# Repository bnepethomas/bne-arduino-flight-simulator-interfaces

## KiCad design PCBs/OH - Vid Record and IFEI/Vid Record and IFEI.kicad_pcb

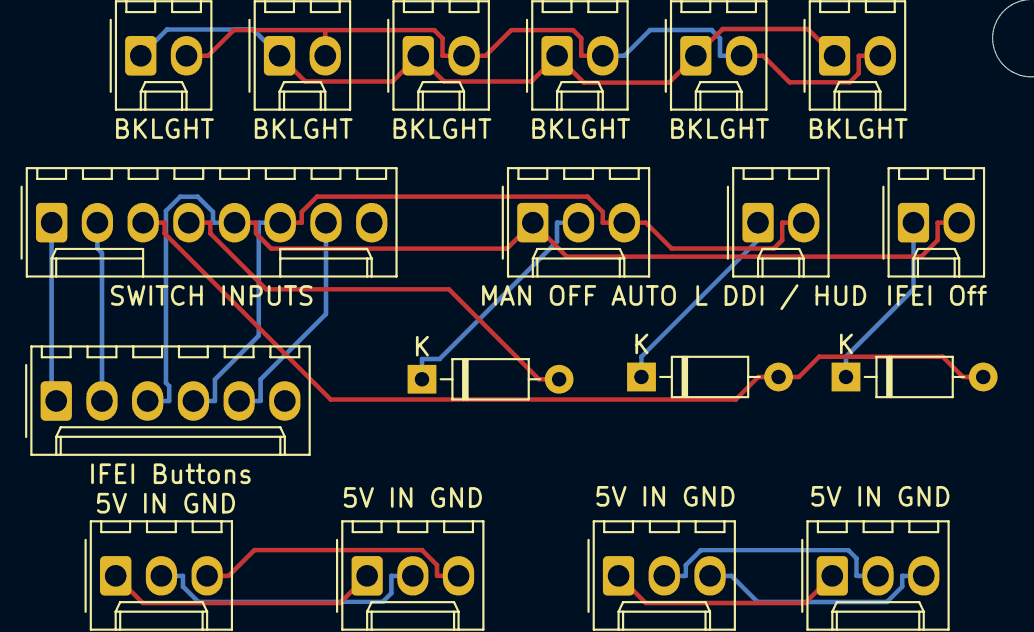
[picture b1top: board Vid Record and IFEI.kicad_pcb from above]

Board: 2 copper layers, 22 parts (0 on the bottom side), 18 nets.

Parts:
D1, D2, D3: D; D_Signal_P7.62mm_Horizontal
H1, H2, H3, H4: MountingHole; MountingHole_4.3mm_M4
J1: IFEI NEXTION; Molex_1x03_P2.54mm_Vertical
J2: IFEI BRIGHTNESS; Molex_1x03_P2.54mm_Vertical
J3: IFEI Buttons; Molex_1x06_P2.54mm_Vertical
J4: SWITCH INPUTS; Molex_1x08_P2.54mm_Vertical
J5, J6, J7, J8, J9, J10: BKLGHT; Molex_1x02_P2.54mm_Vertical
RV1: IFEI NEXTRON; Molex_1x03_P2.54mm_Vertical
RV2: IFEI Brightness; Molex_1x03_P2.54mm_Vertical
SW1: IFEI Off; Molex_1x02_P2.54mm_Vertical
SW2: L DDI / HUD; Molex_1x02_P2.54mm_Vertical
SW3: MAN OFF AUTO; Molex_1x03_P2.54mm_Vertical

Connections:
/BACKLIGHT+12V: J5.1, J6.1, J7.1, J8.1, J9.1, J10.1
/BACKLIGHT-GND: J5.2, J6.2, J7.2, J8.2, J9.2, J10.2
/COL-3: D1.2, D2.2, J4.3
/COL-4: D3.2, J4.4
/IFEI-COL-1: J3.1, J4.1
/IFEI-COL-2: J3.2, J4.2
/IFEI-ROW-1: J3.3, J4.5, SW1.2, SW3.1
/IFEI-ROW-2: J3.4, J4.6, SW2.2, SW3.3
/IFEI-ROW-3: J3.5, J4.7
unnamed: D1.1, SW1.1
unnamed: D2.1, SW2.1
unnamed: D3.1, SW3.2
unnamed: J1.1, RV1.1
unnamed: J1.2, RV1.2
unnamed: J1.3, RV1.3
unnamed: J2.1, RV2.1
unnamed: J2.2, RV2.2
unnamed: J2.3, RV2.3

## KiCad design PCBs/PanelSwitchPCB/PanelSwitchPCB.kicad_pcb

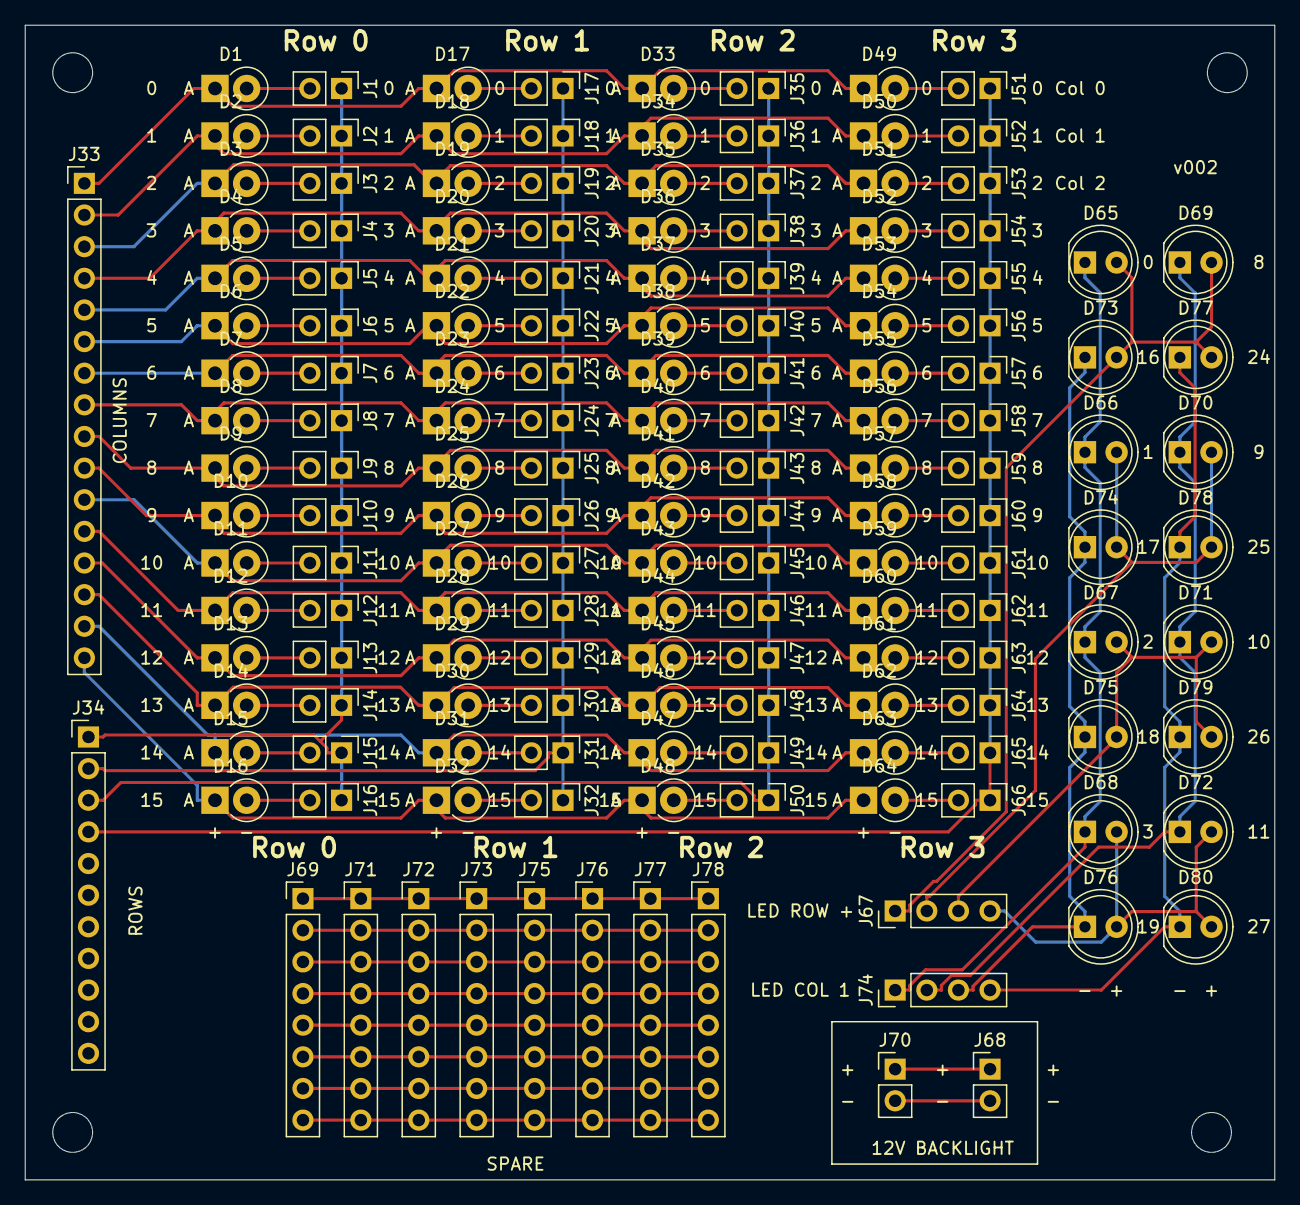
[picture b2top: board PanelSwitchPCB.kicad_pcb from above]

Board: 2 copper layers, 100.3 x 92.7 mm, 162 parts (0 on the bottom side), 102 nets.

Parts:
D1, D2, D3, D4, D5, D6, D7, D8, D9, D10, D11, D12, D13, D14, D15, D16, D17, D18, D19, D20, D21, D22, D23, D24, D25, D26, D27, D28, D29, D30, D31, D32, D33, D34, D35, D36, D37, D38, D39, D40, D41, D42, D43, D44, D45, D46, D47, D48, D49, D50, D51, D52, D53, D54, D55, D56, D57, D58, D59, D60, D61, D62, D63, D64: DIODE; D_DO-41_SOD81_P2.54mm_Vertical_KathodeUp
D65, D66, D67, D68, D69, D70, D71, D72, D73, D74, D75, D76, D77, D78, D79, D80: LD271; LED_D5.0mm_IRGrey
H1, H2, H3, H4: MountingHole_3.2mm_M3
J1, J2, J3, J4, J5, J6, J7, J8, J9, J10, J11, J12, J13, J14, J15, J16, J17, J18, J19, J20, J21, J22, J23, J24, J25, J26, J27, J28, J29, J30, J31, J32, J35, J36, J37, J38, J39, J40, J41, J42, J43, J44, J45, J46, J47, J48, J49, J50, J51, J52, J53, J54, J55, J56, J57, J58, J59, J60, J61, J62, J63, J64, J65, J66, J68, J70: Conn_01x02_Male; PinHeader_1x02_P2.54mm_Vertical
J33: Conn_01x16_Female; PinHeader_1x16_P2.54mm_Vertical
J34: Conn_01x11; PinHeader_1x11_P2.54mm_Vertical
J67, J74: Conn_01x04_Female; PinHeader_1x04_P2.54mm_Vertical
J69, J71, J72, J73, J75, J76, J77, J78: Conn_01x08_Female; PinHeader_1x08_P2.54mm_Vertical

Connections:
/Col0: J1.1, J2.1, J3.1, J4.1, J5.1, J6.1, J7.1, J8.1, J9.1, J10.1, J11.1, J12.1, J13.1, J14.1, J15.1, J16.1, J34.1
/Col1: J17.1, J18.1, J19.1, J20.1, J21.1, J22.1, J23.1, J24.1, J25.1, J26.1, J27.1, J28.1, J29.1, J30.1, J31.1, J32.1, J34.2
/Col2: J34.3, J35.1, J36.1, J37.1, J38.1, J39.1, J40.1, J41.1, J42.1, J43.1, J44.1, J45.1, J46.1, J47.1, J48.1, J49.1, J50.1
/Col3: J34.4, J51.1, J52.1, J53.1, J54.1, J55.1, J56.1, J57.1, J58.1, J59.1, J60.1, J61.1, J62.1, J63.1, J64.1, J65.1, J66.1
/Row0: D1.1, D17.1, D33.1, D49.1, J33.1
/Row1: D2.1, D18.1, D34.1, D50.1, J33.2
/Row2: D3.1, D19.1, D35.1, D51.1, J33.3
/Row3: D4.1, D20.1, D36.1, D52.1, J33.4
/Row4: D5.1, D21.1, D37.1, D53.1, J33.5
/Row5: D6.1, D22.1, D38.1, D54.1, J33.6
/Row6: D7.1, D23.1, D39.1, D55.1, J33.7
/Row7: D8.1, D24.1, D40.1, D56.1, J33.8
/Row8: D9.1, D25.1, D41.1, D57.1, J33.9
/Row9: D10.1, D26.1, D42.1, D58.1, J33.10
/Row10: D11.1, D27.1, D43.1, D59.1, J33.11
/Row11: D12.1, D28.1, D44.1, D60.1, J33.12
/Row12: D13.1, D29.1, D45.1, D61.1, J33.13
/Row13: D14.1, D30.1, D46.1, D62.1, J33.14
/Row14: D15.1, D31.1, D47.1, D63.1, J33.15
/Row15: D16.1, D32.1, D48.1, D64.1, J33.16
/Spare0: J69.1, J71.1, J72.1, J73.1, J75.1, J76.1, J77.1, J78.1
/Spare1: J69.2, J71.2, J72.2, J73.2, J75.2, J76.2, J77.2, J78.2
/Spare2: J69.3, J71.3, J72.3, J73.3, J75.3, J76.3, J77.3, J78.3
/Spare3: J69.4, J71.4, J72.4, J73.4, J75.4, J76.4, J77.4, J78.4
/Spare4: J69.5, J71.5, J72.5, J73.5, J75.5, J76.5, J77.5, J78.5
/Spare5: J69.6, J71.6, J72.6, J73.6, J75.6, J76.6, J77.6, J78.6
/Spare6: J69.7, J71.7, J72.7, J73.7, J75.7, J76.7, J77.7, J78.7
/Spare7: J69.8, J71.8, J72.8, J73.8, J75.8, J76.8, J77.8, J78.8
unnamed: D1.2, J1.2
unnamed: D2.2, J2.2
unnamed: D3.2, J3.2
unnamed: D4.2, J4.2
unnamed: D5.2, J5.2
unnamed: D6.2, J6.2
unnamed: D7.2, J7.2
unnamed: D8.2, J8.2
unnamed: D9.2, J9.2
unnamed: D10.2, J10.2
unnamed: D11.2, J11.2
unnamed: D12.2, J12.2
unnamed: D13.2, J13.2
unnamed: D14.2, J14.2
unnamed: D15.2, J15.2
unnamed: D16.2, J16.2
unnamed: D17.2, J17.2
unnamed: D18.2, J18.2
unnamed: D19.2, J19.2
unnamed: D20.2, J20.2
unnamed: D21.2, J21.2
unnamed: D22.2, J22.2
unnamed: D23.2, J23.2
unnamed: D24.2, J24.2
unnamed: D25.2, J25.2
unnamed: D26.2, J26.2
unnamed: D27.2, J27.2
unnamed: D28.2, J28.2
unnamed: D29.2, J29.2
unnamed: D30.2, J30.2
unnamed: D31.2, J31.2
unnamed: D32.2, J32.2
unnamed: D33.2, J35.2
unnamed: D34.2, J36.2
unnamed: D35.2, J37.2
unnamed: D36.2, J38.2
unnamed: D37.2, J39.2
unnamed: D38.2, J40.2
unnamed: D39.2, J41.2
unnamed: D40.2, J42.2
unnamed: D41.2, J43.2
unnamed: D42.2, J44.2
unnamed: D43.2, J45.2
unnamed: D44.2, J46.2
unnamed: D45.2, J47.2
unnamed: D46.2, J48.2
unnamed: D47.2, J49.2
unnamed: D48.2, J50.2
unnamed: D49.2, J51.2
unnamed: D50.2, J52.2
unnamed: D51.2, J53.2
unnamed: D52.2, J54.2
unnamed: D53.2, J55.2
unnamed: D54.2, J56.2
unnamed: D55.2, J57.2
unnamed: D56.2, J58.2
unnamed: D57.2, J59.2
unnamed: D58.2, J60.2
unnamed: D59.2, J61.2
unnamed: D60.2, J62.2
unnamed: D61.2, J63.2
unnamed: D62.2, J64.2
unnamed: D63.2, J65.2
unnamed: D64.2, J66.2
unnamed: D65.1, D66.1, D67.1, D68.1, J74.1
unnamed: D65.2, D69.2, D73.2, D77.2, J67.1
unnamed: D66.2, D70.2, D74.2, D78.2, J67.2
unnamed: D67.2, D71.2, D75.2, D79.2, J67.3
unnamed: D68.2, D72.2, D76.2, D80.2, J67.4
unnamed: D69.1, D70.1, D71.1, D72.1, J74.2
unnamed: D73.1, D74.1, D75.1, D76.1, J74.3
unnamed: D77.1, D78.1, D79.1, D80.1, J74.4
unnamed: J68.1, J70.1
unnamed: J68.2, J70.2

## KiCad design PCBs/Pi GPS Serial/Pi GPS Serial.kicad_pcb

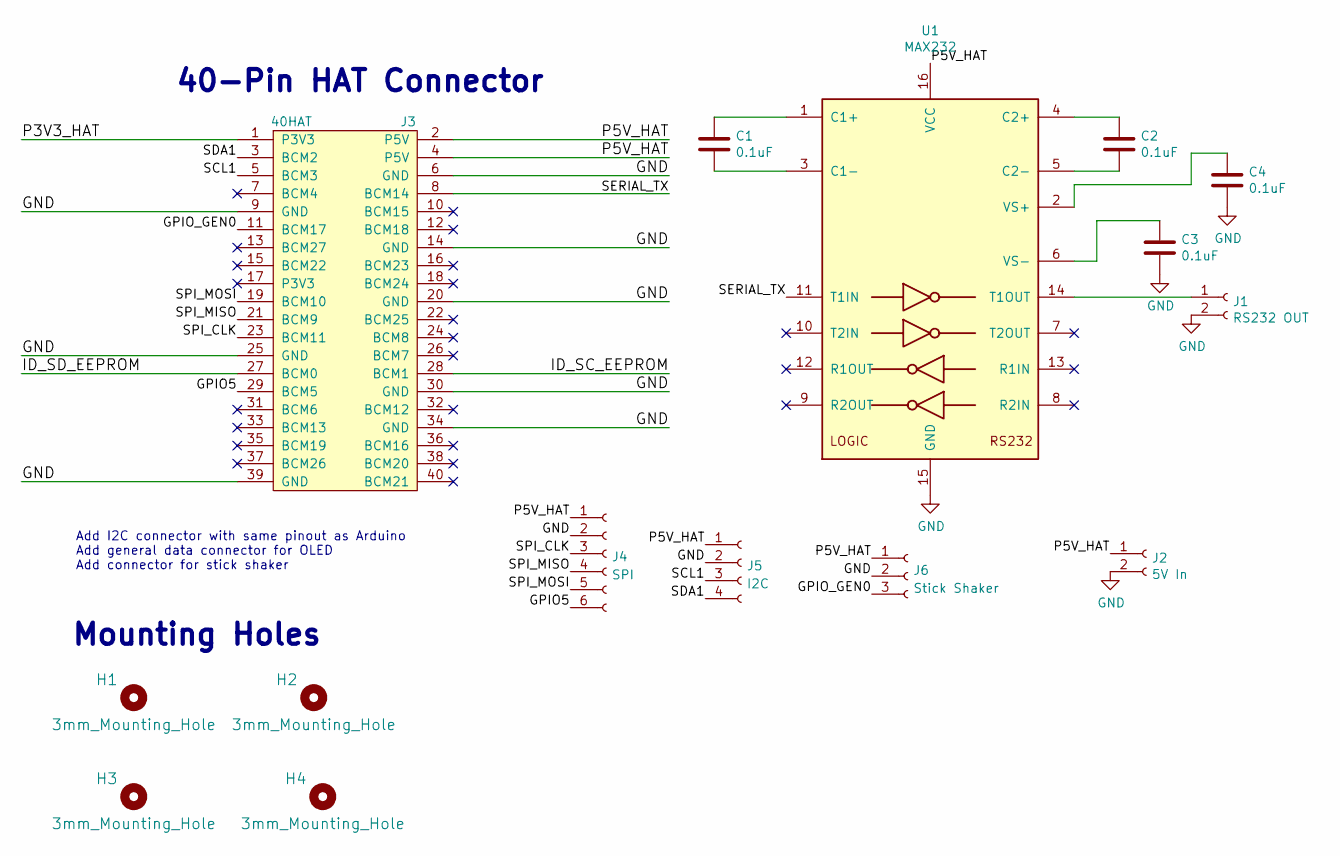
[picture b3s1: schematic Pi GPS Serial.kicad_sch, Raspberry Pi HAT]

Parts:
C1, C2, C3, C4: 0.1uF; C_Disc_D4.3mm_W1.9mm_P5.00mm
H1, H2, H3, H4: 3mm_Mounting_Hole; NPTH_3mm_ID
J1: RS232 OUT; Molex_1x02_P2.54mm_Vertical
J2: 5V In; Molex_1x02_P2.54mm_Vertical
J3: 40HAT; PinSocket_2x20_P2.54mm_Vertical
J4: SPI; Molex_KK-254_AE-6410-06A_1x06_P2.54mm_Vertical
J5: I2C; Molex_KK-254_AE-6410-04A_1x04_P2.54mm_Vertical
J6: Stick Shaker; Molex_KK-254_AE-6410-03A_1x03_P2.54mm_Vertical
U1: MAX232; DIP-16_W7.62mm

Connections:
/GPIO5: J3.29 (BCM5), J4.6
/GPIO_GEN0: J3.11 (BCM17), J6.3
/ID_SC_EEPROM: J3.28 (BCM1)
/ID_SD_EEPROM: J3.27 (BCM0)
/P3V3_HAT: J3.1 (P3V3)
/P5V_HAT: J2.1, J3.2 (P5V), J3.4 (P5V), J4.1, J5.1, J6.1, U1.16 (VCC)
/SCL1: J3.5 (BCM3), J5.3
/SDA1: J3.3 (BCM2), J5.4
/SERIAL_TX: J3.8 (BCM14), U1.11 (T1IN)
/SPI_CLK: J3.23 (BCM11), J4.3
/SPI_MISO: J3.21 (BCM9), J4.4
/SPI_MOSI: J3.19 (BCM10), J4.5
GND: C3.2, C4.2, J1.2, J2.2, J3.6 (GND), J3.9 (GND), J3.14 (GND), J3.20 (GND), J3.25 (GND), J3.30 (GND), J3.34 (GND), J3.39 (GND), J4.2, J5.2, J6.2, U1.15 (GND)
unnamed: C1.1, U1.1 (C1+)
unnamed: C1.2, U1.3 (C1-)
unnamed: C2.1, U1.4 (C2+)
unnamed: C2.2, U1.5 (C2-)
unnamed: J1.1, U1.14 (T1OUT)
unnamed: C4.1, U1.2 (VS+)
unnamed: C3.1, U1.6 (VS-)

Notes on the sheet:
Mounting Holes
Add I2C connector with same pinout as Arduino Add general data connector for OLED Add connector for stick shaker
40-Pin HAT Connector

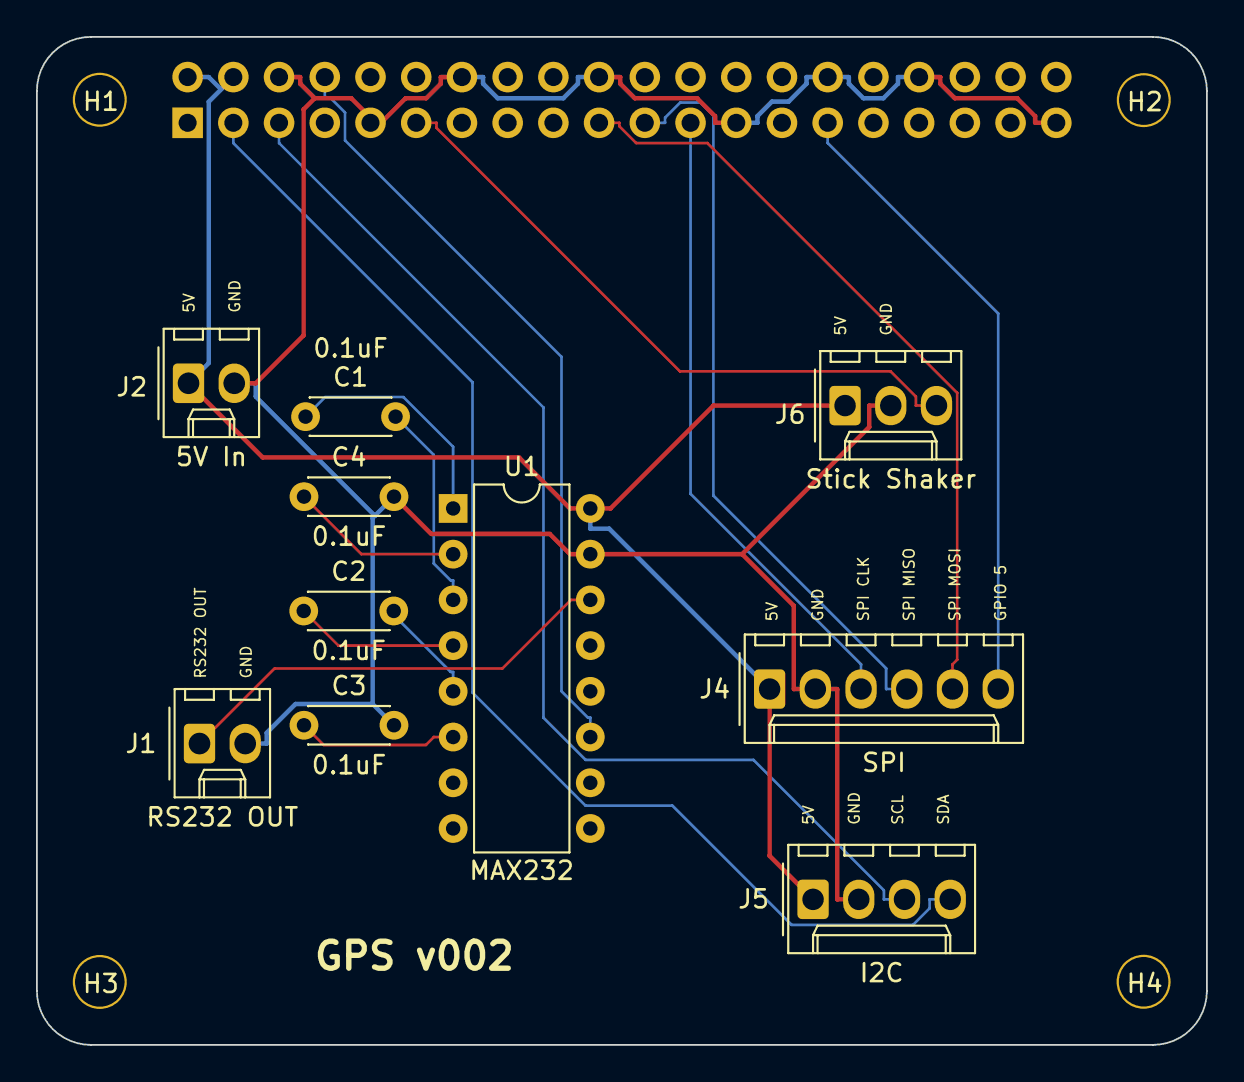
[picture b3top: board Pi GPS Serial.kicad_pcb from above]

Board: 2 copper layers, 65.0 x 56.0 mm, 15 parts (1 on the bottom side), 17 nets.

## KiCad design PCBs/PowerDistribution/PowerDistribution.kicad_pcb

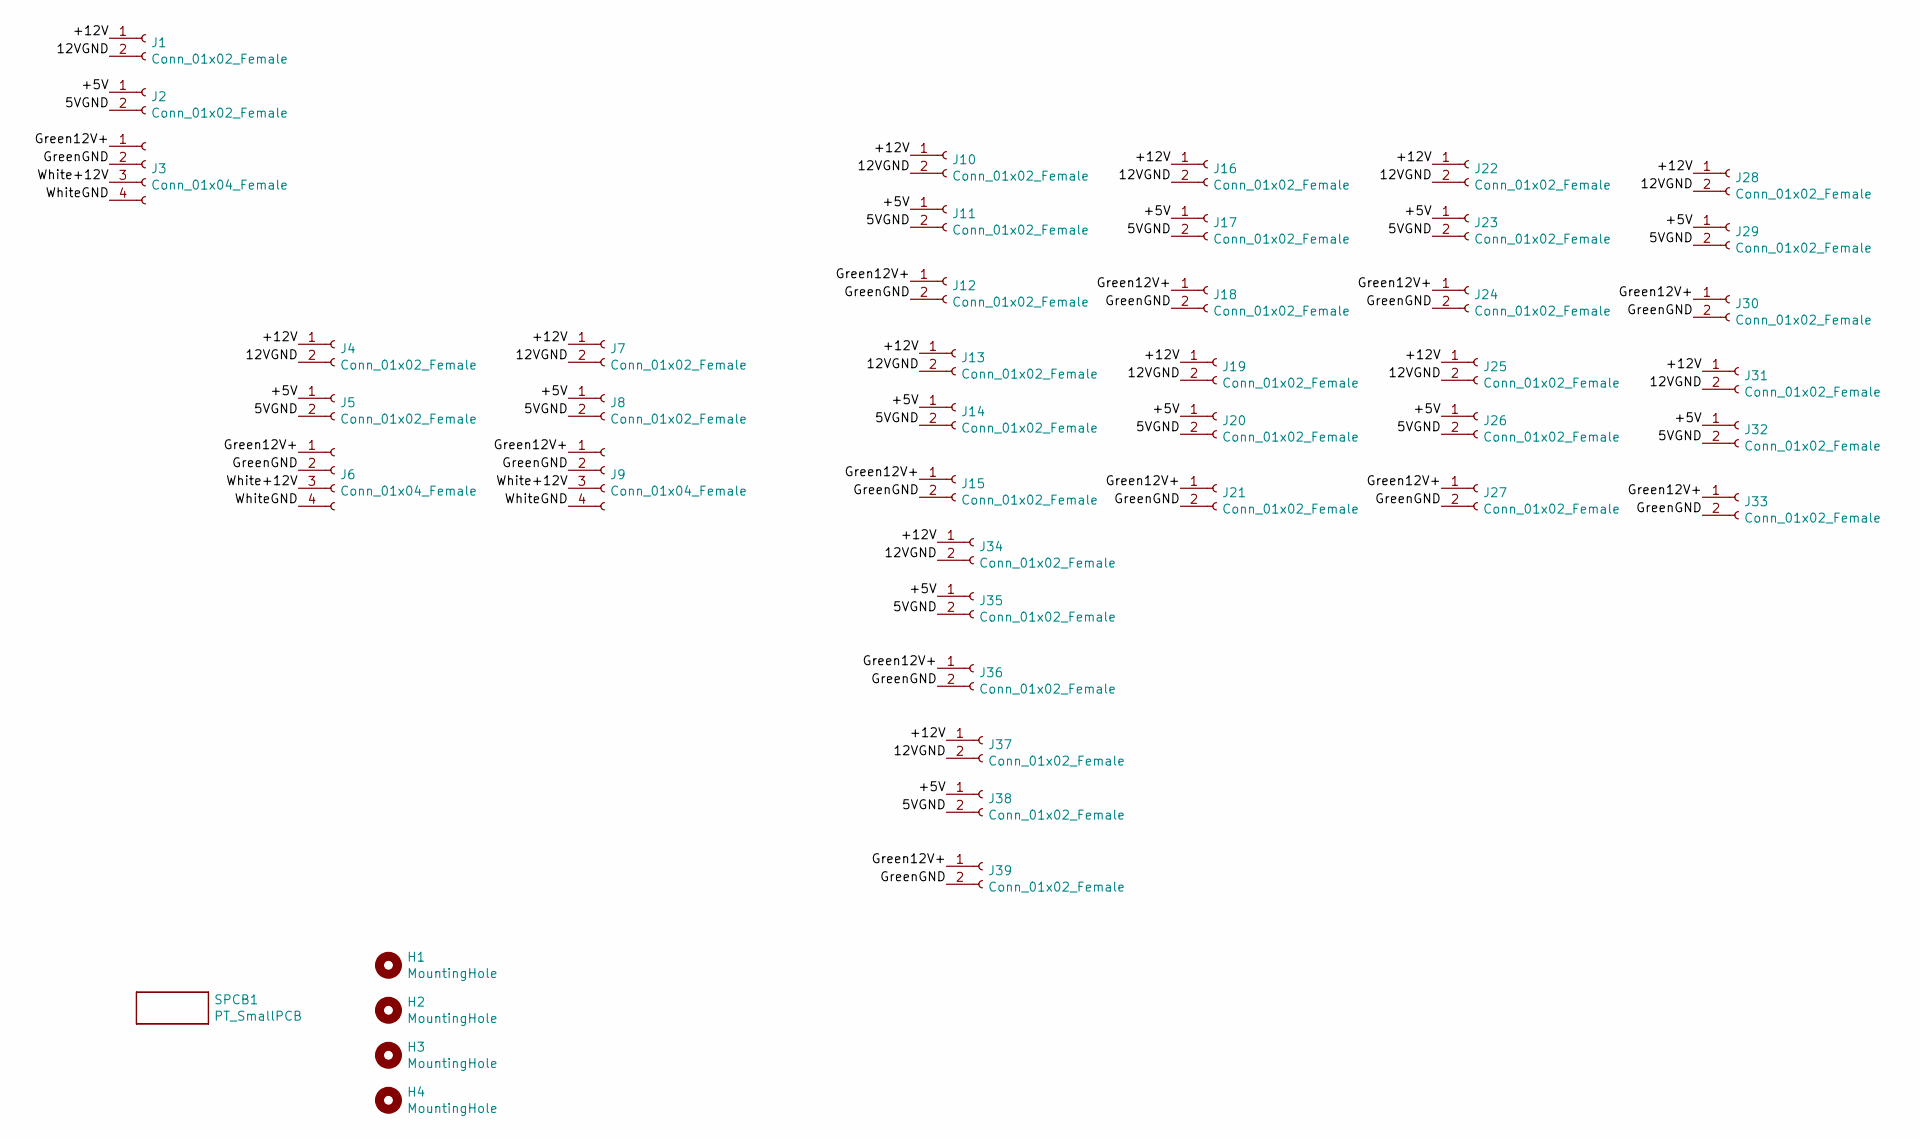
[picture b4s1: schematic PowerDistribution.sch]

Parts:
H1, H2, H3, H4: MountingHole; MountingHole_3.2mm_M3
J1, J2: Conn_01x02_Female; TerminalBlock_bornier-2_P5.08mm
J3, J6, J9: Conn_01x04_Female; Molex_1x04_P2.54mm_Vertical
J4, J5, J7, J8, J10, J11, J12, J13, J14, J15, J16, J17, J18, J19, J20, J21, J22, J23, J24, J25, J26, J27, J28, J29, J30, J31, J32, J33, J34, J35, J36, J37, J38, J39: Conn_01x02_Female; Molex_1x02_P2.54mm_Vertical
SPCB1: PT_SmallPCB; PT_General_PCB_Outline

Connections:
/5VGND: J2.2, J5.2, J8.2, J11.2, J14.2, J17.2, J20.2, J23.2, J26.2, J29.2, J32.2, J35.2, J38.2; also elsewhere on the board
/12VGND: J1.2, J4.2, J7.2, J10.2, J13.2, J16.2, J19.2, J22.2, J25.2, J28.2, J31.2, J34.2, J37.2; also elsewhere on the board
/+5V: J2.1, J5.1, J8.1, J11.1, J14.1, J17.1, J20.1, J23.1, J26.1, J29.1, J32.1, J35.1, J38.1; also elsewhere on the board
/+12V: J1.1, J4.1, J7.1, J10.1, J13.1, J16.1, J19.1, J22.1, J25.1, J28.1, J31.1, J34.1, J37.1; also elsewhere on the board
/Green12V+: J3.1, J6.1, J9.1, J12.1, J15.1, J18.1, J21.1, J24.1, J27.1, J30.1, J33.1, J36.1, J39.1
/GreenGND: J3.2, J6.2, J9.2, J12.2, J15.2, J18.2, J21.2, J24.2, J27.2, J30.2, J33.2, J36.2, J39.2
/White+12V: J3.3, J6.3, J9.3
/WhiteGND: J3.4, J6.4, J9.4

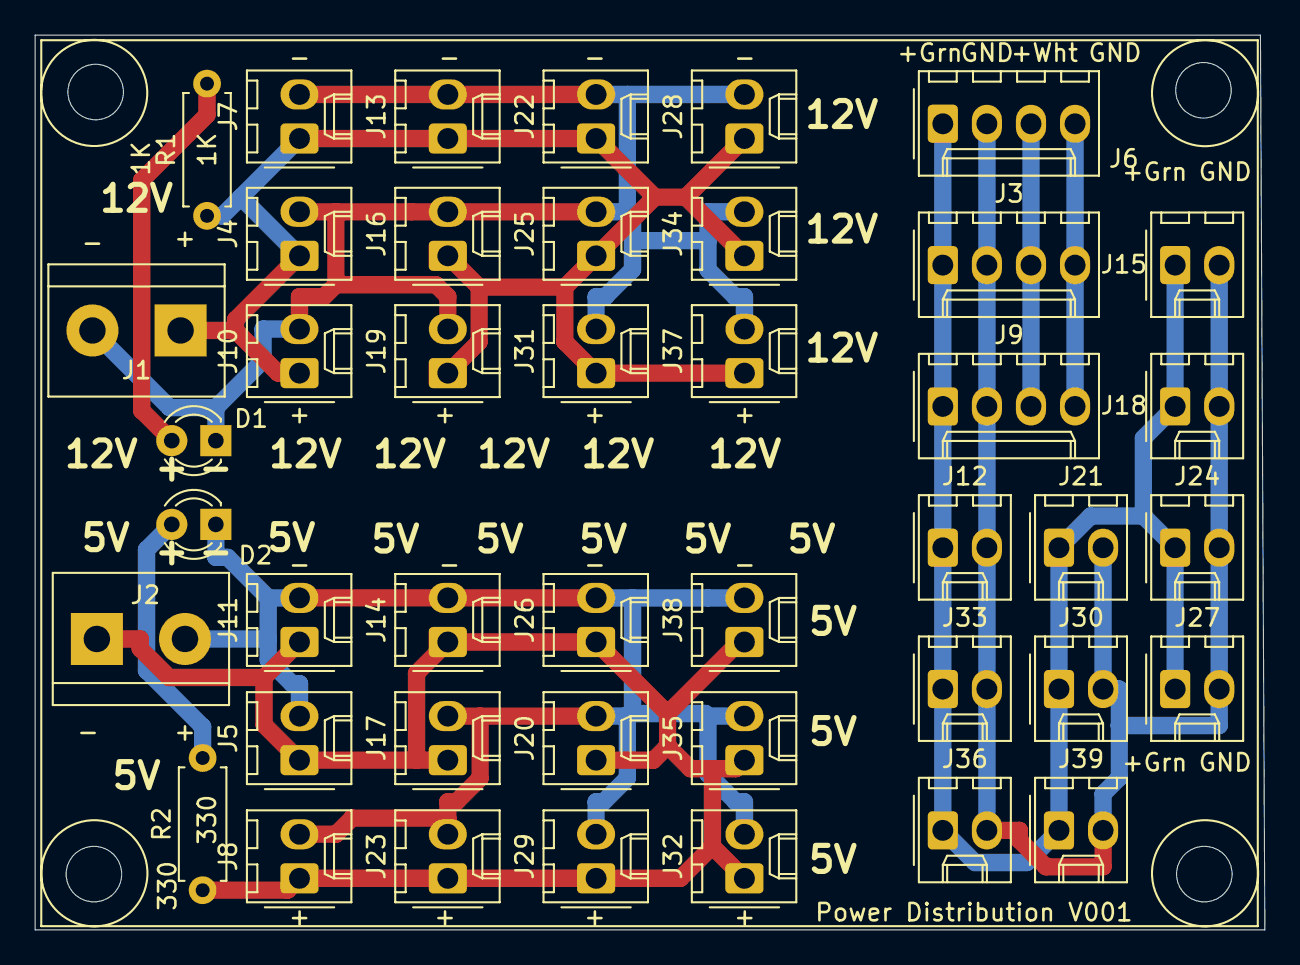
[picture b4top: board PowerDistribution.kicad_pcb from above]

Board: 2 copper layers, 70.9 x 51.6 mm, 48 parts (0 on the bottom side), 10 nets.

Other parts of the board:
D1, D2: LED; LED_D3.0mm
R1: 1K; R_Axial_DIN0207_L6.3mm_D2.5mm_P7.62mm_Horizontal
R2: 330; R_Axial_DIN0207_L6.3mm_D2.5mm_P7.62mm_Horizontal

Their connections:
/5VGND: D2.1; also elsewhere on the board
/12VGND: D1.1; also elsewhere on the board
/+5V: R2.1; also elsewhere on the board
/+12V: R1.1; also elsewhere on the board
unnamed: D1.2, R1.2
unnamed: D2.2, R2.2

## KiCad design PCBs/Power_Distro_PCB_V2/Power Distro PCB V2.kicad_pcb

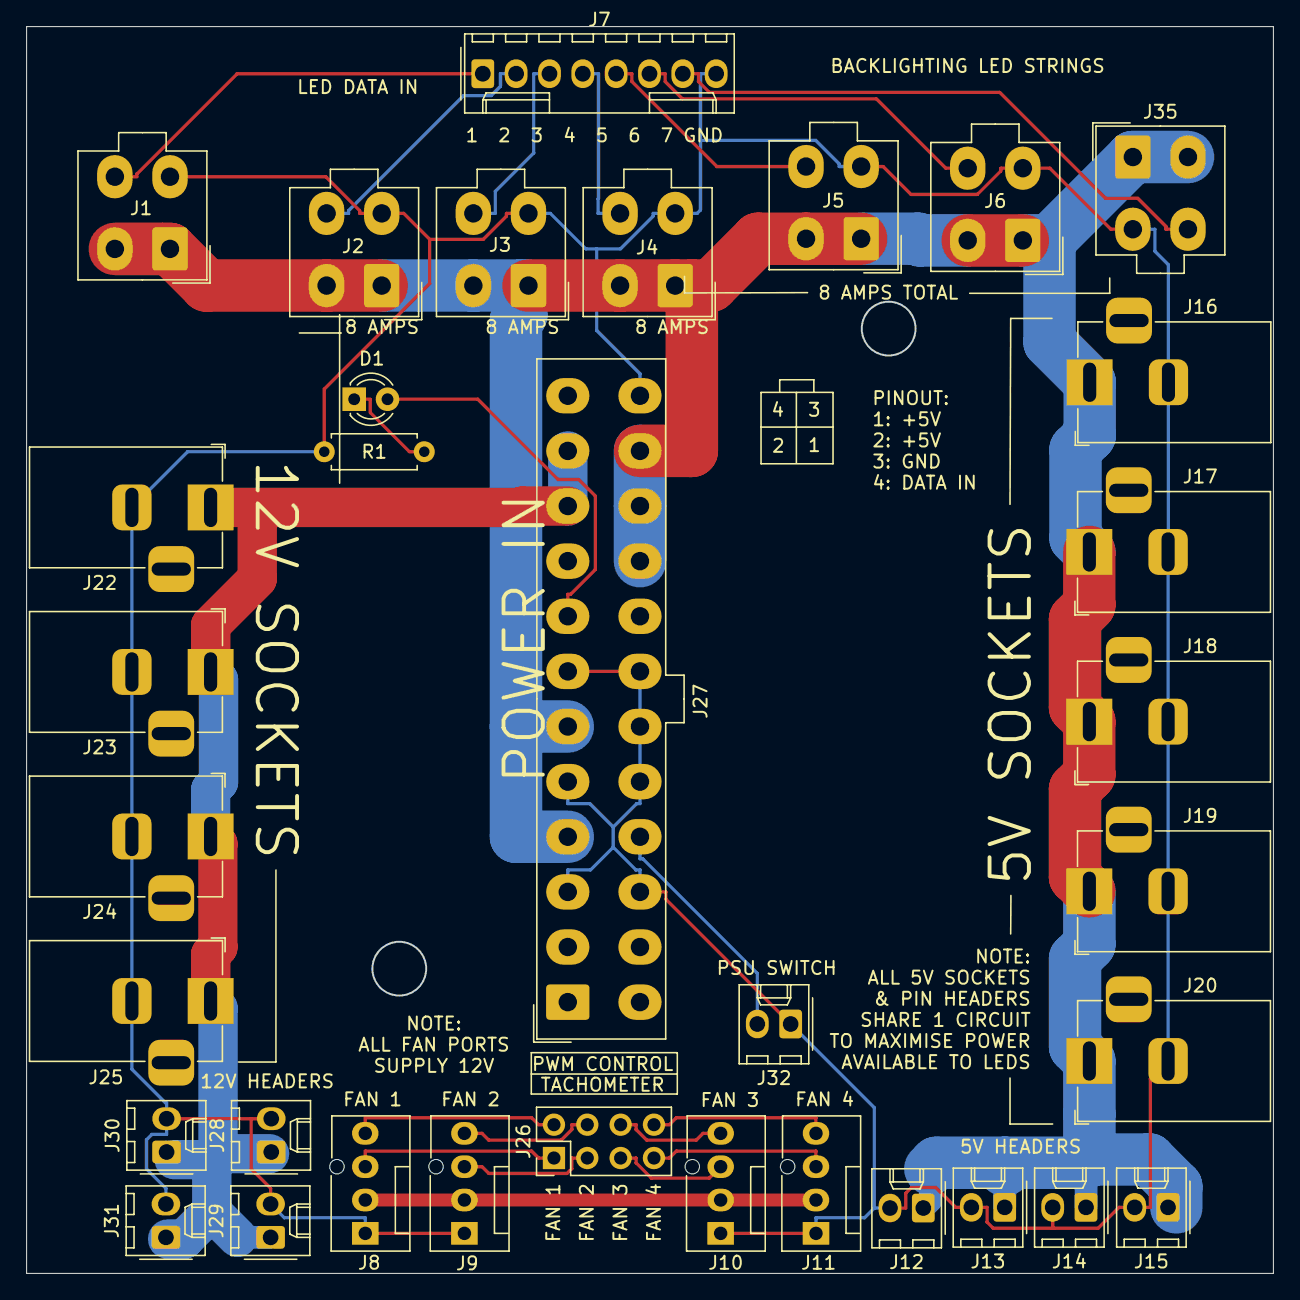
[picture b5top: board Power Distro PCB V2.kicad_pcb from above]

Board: 2 copper layers, 95.0 x 95.0 mm, 34 parts (0 on the bottom side), 22 nets.

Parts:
D1: LED; LED_D3.0mm
J1, J2, J3, J4, J5, J6, J35: Conn_01x04_Female; Molex_Mini-Fit_Jr_5566-04A_2x02_P4.20mm_Vertical
J7: Conn_01x08_Female; Molex_1x08_P2.54mm_Vertical
J8, J9, J10, J11: Conn_01x04_Female; FanPinHeader_1x04_P2.54mm_Vertical
J12, J13, J14, J15, J28, J29, J30, J31, J32: Conn_01x02_Female; Molex_KK-254_AE-6410-02A_1x02_P2.54mm_Vertical
J16, J17, J18, J19, J20, J22, J23, J24, J25: Conn_01x02_Female; BarrelJack_Horizontal
J26: Conn_01x08_Female; PinHeader_2x04_P2.54mm_Vertical
J27: Conn_01x24_Female; Molex_Mini-Fit_Jr_5566-24A_2x12_P4.20mm_Vertical
R1: R; R_Axial_DIN0207_L6.3mm_D2.5mm_P7.62mm_Horizontal

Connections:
/12VSOCKETS+: J22.1, J23.1, J24.1, J25.1, J27.10, J27.11, J28.1, J29.1, J30.1, J31.1
/FAN1Control: J8.4, J26.2
/FAN1Tach: J8.3, J26.1
/FAN2Control: J9.4, J26.4
/FAN2Tach: J9.3, J26.3
/FAN3Control: J10.4, J26.6
/FAN3Tach: J10.3, J26.5
/FAN4Control: J11.4, J26.8
/FAN4Tach: J11.3, J26.7
/FAN+: J8.2, J9.2, J10.2, J11.2
/LED5V1: J1.1, J1.2, J2.1, J2.2, J3.1, J3.2, J4.1, J4.2, J5.1, J5.2, J6.1, J6.2, J12.1, J13.1, J14.1, J15.1, J16.1, J17.1, J18.1, J19.1, J20.1, J27.4, J27.6, J27.21, J27.22, J27.23, J35.1, J35.2
/LEDDATA1: J1.4, J7.1
/LEDDATA2: J2.4, J7.2
/LEDDATA3: J3.4, J7.3
/LEDDATA4: J4.4, J7.4
/LEDDATA5: J5.4, J7.5
/LEDDATA6: J6.4, J7.6
/LEDDATA7: J7.7, J35.4
/LEDGND: J1.3, J2.3, J3.3, J4.3, J5.3, J6.3, J7.8, J8.1, J9.1, J10.1, J11.1, J12.2, J13.2, J14.2, J15.2, J16.2, J17.2, J18.2, J19.2, J20.2, J22.2, J23.2, J24.2, J25.2, J27.3, J27.5, J27.7, J27.15, J27.17, J27.18, J27.19, J27.24, J28.2, J29.2, J30.2, J31.2, J32.1, J35.3, R1.1
/PSUSW: J27.16, J32.2
/PWRGOOD: D1.2, J27.8
unnamed: D1.1, R1.2

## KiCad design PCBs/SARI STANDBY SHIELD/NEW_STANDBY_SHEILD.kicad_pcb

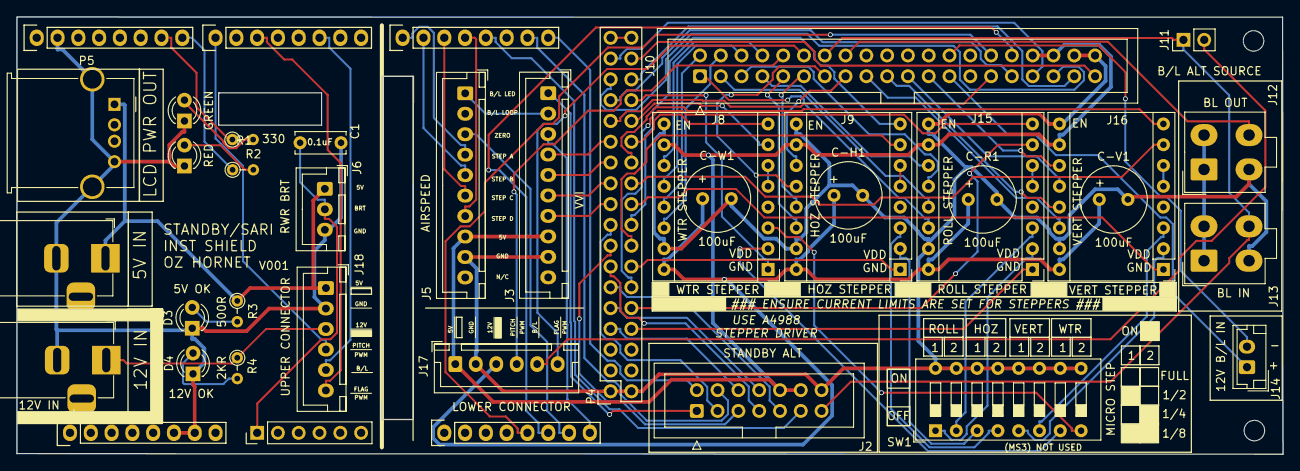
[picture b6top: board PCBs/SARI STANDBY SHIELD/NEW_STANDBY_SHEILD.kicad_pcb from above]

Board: 2 copper layers, 154.7 x 53.4 mm, 41 parts (0 on the bottom side), 94 nets.

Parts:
C1: 0.1uF; C_Disc_D6.0mm_W2.5mm_P5.00mm
C-H1: 100uF; C_Radial_D8.0mm_H7.0mm_P3.50mm
C-R1: 100uF; C_Radial_D8.0mm_H7.0mm_P3.50mm
C-V1: 100uF; C_Radial_D8.0mm_H7.0mm_P3.50mm
C-W1: 100uF; C_Radial_D8.0mm_H7.0mm_P3.50mm
D1: GREEN; LED_D3.0mm
D2: RED; LED_D3.0mm
D3, D4: LED; LED_D3.0mm
H1: H1; MountingHole_2.5mm
H2: H2; MountingHole_2.5mm
J1: TO LCD; USB_A_Molex_67643_Horizontal
J2: STANDBY ALT; IDC-Header_2x07_P2.54mm_Vertical
J3: VVI; JST_XH_B10B-XH-A_1x10_P2.50mm_Vertical
J4: 5V IN; BarrelJack_Horizontal
J5: AIRSPEED; JST_XH_B10B-XH-A_1x10_P2.50mm_Vertical
J6: RWR BRT; JST_XH_B3B-XH-A_1x03_P2.50mm_Vertical
J7: STEPPER IN 12-20VDC; BarrelJack_Horizontal
J8: WTR STEPPER; Pololu_Breakout-16_15.2x20.3mm
J9: HOZ STEPPER; Pololu_Breakout-16_15.2x20.3mm
J10: TO SARI PCB; IDC-Header_2x20_P2.54mm_Vertical
J11: B/L ALT SOURCE; PinHeader_1x02_P2.54mm_Vertical
J12: BL OUT; Molex_Mini-Fit_Jr_5566-04A_2x02_P4.20mm_Vertical
J13: BL IN; Molex_Mini-Fit_Jr_5566-04A_2x02_P4.20mm_Vertical
J14: 12V B/L IN; JST_EH_B2B-EH-A_1x02_P2.50mm_Vertical
J15: ROLL STEPPER; Pololu_Breakout-16_15.2x20.3mm
J16: VERT STEPPER; Pololu_Breakout-16_15.2x20.3mm
J17: LOWER CONNECTOR; JST_XH_B6B-XH-A_1x06_P2.50mm_Vertical
J18: UPPER CONNECTOR; JST_XH_B6B-XH-A_1x06_P2.50mm_Vertical
P1: Power; Socket_Strip_Arduino_1x08
P2: Analog; PinHeader_1x06_P2.54mm_Vertical
P3: Analog; Socket_Strip_Arduino_1x08
P4: Digital; Socket_Strip_Arduino_2x18
P5, P6: PWM; Socket_Strip_Arduino_1x08
P7: Communication; Socket_Strip_Arduino_1x08
R1: 330; R_Axial_DIN0204_L3.6mm_D1.6mm_P2.54mm_Vertical
R2: 330; PT_R_Axial_DIN0204_L3.6mm_D1.6mm_P2.54mm_Vertical
R3: 500; R_Axial_DIN0204_L3.6mm_D1.6mm_P2.54mm_Vertical
R4: 2000; R_Axial_DIN0204_L3.6mm_D1.6mm_P2.54mm_Vertical
SW1: MICRO STEP; SW_DIP_SPSTx08_Slide_9.78x22.5mm_W7.62mm_P2.54mm

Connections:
/AIR_COIL_A: J5.4, P7.1
/AIR_COIL_B: J5.5, P7.2
/AIR_COIL_C: J5.6, P7.3
/AIR_COIL_D: J5.7, P7.4
/AIR_ZERO_DET: J5.3, P3.7
/ALT_B/L_LOWER: J11.2, J17.5
/ALT_B/L_UPPER: J18.5, P6.6
/ALT_COIL_A: J2.7, P4.13
/ALT_COIL_B: J2.9, P4.11
/ALT_COIL_C: J2.3, P4.17
/ALT_COIL_D: J2.5, P4.15
/ALT_ENC_A: J2.6, P4.7
/ALT_ENC_B: J2.8, P4.9
/ALT_ZERO_DET: J2.11, P7.5
/BACK/LT_+: J10.25, J14.1
/BACK/LT_-: J10.26, J14.2
/ENCODER_A: J10.29, P4.27
/ENCODER_B: J10.31, P4.29
/ENCODER_PUSH: J10.32, P3.6
/GREEN_LED: P5.7, R1.1
/HOZ_1A: J9.13, J10.11
/HOZ_1B: J9.14, J10.9
/HOZ_2A: J9.12, J10.13
/HOZ_2B: J9.11, J10.15
/HOZ_DIR: J9.8, P4.18
/HOZ_EN: J9.1, P4.14
/HOZ_MS1: J9.2, SW1.3
/HOZ_MS2: J9.3, SW1.4
/HOZ_STEP: J9.7, P4.16
/HOZ_STEP_GND: C-H1.2, C-R1.2, C-V1.2, C-W1.2, J2.14, J3.9, J5.9, J8.9, J8.15, J9.9, J9.15, J10.38, J10.40, J12.3, J13.3, J15.9, J15.15, J16.9, J16.15, J17.2, P4.1, P4.2, SW1.9, SW1.10, SW1.11, SW1.12, SW1.13, SW1.14, SW1.15, SW1.16
/HOZ_STEP_V+: C-H1.1, C-R1.1, C-V1.1, C-W1.1, J8.16, J9.16, J15.16, J16.16, J17.3
/HOZ_ZERO_IR: J10.35, P4.31
/LED+5V: J12.1, J12.2, J13.1, J13.2
/LED_DATA_IN: J2.13, J10.14, J11.1, J13.4
/LED_DATA_LOOP_1: J2.1, J3.1
/LED_DATA_LOOP_2: J3.2, J5.1
/LED_DATA_OUT: J10.16, J12.4
/LOWER_OUTPUT_5V: J2.10, J2.12, J3.8, J5.8, J8.10, J9.10, J10.34, J10.36, J15.10, J16.10, J17.1
/RED_LED: P5.8, R2.1
/ROLL_1A: J10.3, J15.13
/ROLL_1B: J10.1, J15.14
/ROLL_2A: J10.5, J15.12
/ROLL_2B: J10.7, J15.11
/ROLL_DIR: J15.8, P4.12
/ROLL_EN: J15.1, P4.8
/ROLL_MS1: J15.2, SW1.1
/ROLL_MS2: J15.3, SW1.2
/ROLL_STEP: J15.7, P4.10
/ROLL_ZERO_IR: J10.33, P4.33
/RWR_BRT_ANA: C1.1, J6.2, P2.1
/SCL: J2.2, P7.8
/SDA: J2.4, P7.7
/SERVO_FLAG: J10.12, J17.6
/SERVO_FLAG_U: J18.6, P6.3
/SERVO_PITCH: J10.10, J17.4
/SERVO_PITCH_U: J18.4, P6.1
/TEST_PUSH: J10.30, P3.5
/UPPER_OUTPUT_5V: J1.1 (VBUS), J4.1, J6.1, J18.1, R3.1
/UPPER_OUTPUT_12V: J7.1, J18.3, R4.1
/VER_1A: J10.19, J16.13
/VER_1B: J10.17, J16.14
/VER_2A: J10.21, J16.12
/VER_2B: J10.23, J16.11
/VER_DIR: J16.8, P4.24
/VER_EN: J16.1, P4.20
/VER_MS1: J16.2, SW1.5
/VER_MS2: J16.3, SW1.6
/VER_STEP: J16.7, P4.22
/VER_ZERO_IR: J10.37, P4.32
/VVI_COIL_A: J3.4, P4.25
/VVI_COIL_B: J3.5, P4.23
/VVI_COIL_C: J3.6, P4.21
/VVI_COIL_D: J3.7, P4.19
/VVI_ZERO_DET: J3.3, P3.8
/WL_1A: J8.13, J10.2
/WL_1B: J8.14, J10.4
/WL_2A: J8.12, J10.6
/WL_2B: J8.11, J10.8
/WL_DIR: J8.8, P4.26
/WL_EN: J8.1, P4.30
/WL_MS1: J8.2, SW1.7
/WL_MS2: J8.3, SW1.8
/WL_STEP: J8.7, P4.28
/WL_ZERO_IR: J10.39, P4.34
GNDD: C1.2, D1.1 (K), D2.1 (K), D3.1 (K), D4.1 (K), J1.4 (GND), J1.5 (Shield), J4.2, J6.3, J7.2, J18.2, P1.6, P1.7, P5.2
unnamed: D1.2 (A), R1.2
unnamed: D2.2 (A), R2.2
unnamed: D3.2 (A), R3.2
unnamed: D4.2 (A), R4.2
unnamed: J8.5, J8.6
unnamed: J9.5, J9.6
unnamed: J15.5, J15.6
unnamed: J16.5, J16.6
unnamed: P4.35, P4.36

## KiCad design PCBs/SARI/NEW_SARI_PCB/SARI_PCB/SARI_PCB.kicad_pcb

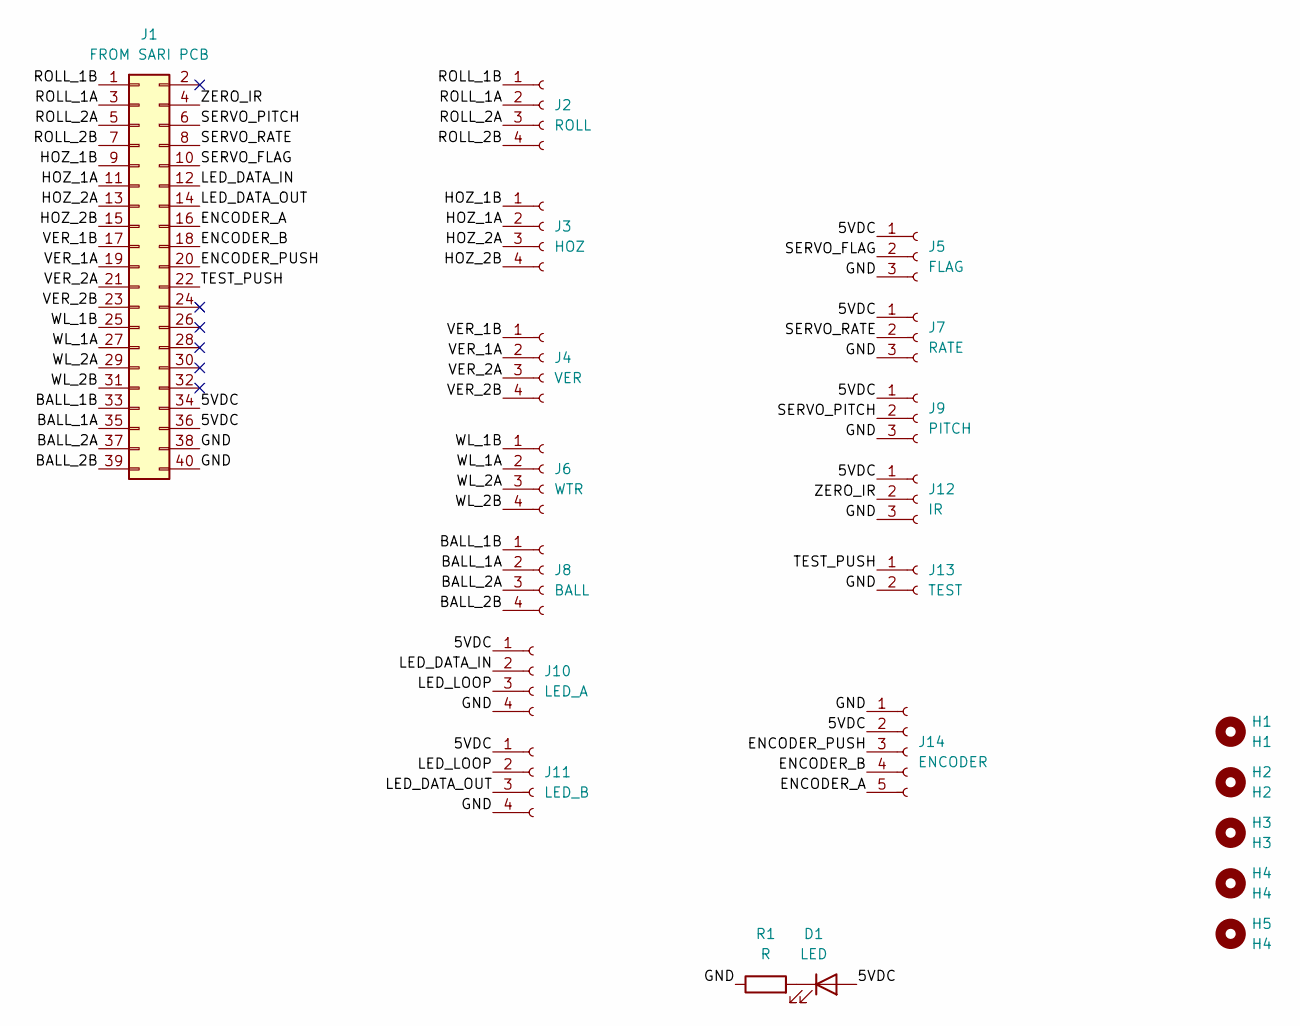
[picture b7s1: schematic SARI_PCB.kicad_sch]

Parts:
D1: LED; LED_D3.0mm
H1: H1; MountingHole_2.5mm
H2: H2; MountingHole_2.5mm
H3: H3; MountingHole_2.5mm
H4, H5: H4; MountingHole_2.5mm
J1: FROM SARI PCB; IDC-Header_2x20_P2.54mm_Vertical
J2: ROLL; JST_XH_B4B-XH-A_1x04_P2.50mm_Vertical
J3: HOZ; JST_XH_B4B-XH-A_1x04_P2.50mm_Vertical
J4: VER; JST_XH_B4B-XH-A_1x04_P2.50mm_Vertical
J5: FLAG; JST_XH_B3B-XH-A_1x03_P2.50mm_Vertical
J6: WTR; JST_XH_B4B-XH-A_1x04_P2.50mm_Vertical
J7: RATE; JST_XH_B3B-XH-A_1x03_P2.50mm_Vertical
J8: BALL; JST_XH_B4B-XH-A_1x04_P2.50mm_Vertical
J9: PITCH; JST_XH_B3B-XH-A_1x03_P2.50mm_Vertical
J10: LED_A; JST_XH_B4B-XH-A_1x04_P2.50mm_Vertical
J11: LED_B; JST_XH_B4B-XH-A_1x04_P2.50mm_Vertical
J12: IR; JST_XH_B3B-XH-A_1x03_P2.50mm_Vertical
J13: TEST; JST_XH_B2B-XH-A_1x02_P2.50mm_Vertical
J14: ENCODER; JST_XH_B5B-XH-A_1x05_P2.50mm_Vertical
R1: R; R_Axial_DIN0207_L6.3mm_D2.5mm_P7.62mm_Horizontal

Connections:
/5VDC: D1.2 (A), J1.34, J1.36, J5.1, J7.1, J9.1, J10.1, J11.1, J12.1, J14.2
/BALL_1A: J1.35, J8.2
/BALL_1B: J1.33, J8.1
/BALL_2A: J1.37, J8.3
/BALL_2B: J1.39, J8.4
/ENCODER_A: J1.16, J14.5
/ENCODER_B: J1.18, J14.4
/ENCODER_PUSH: J1.20, J14.3
/GND: J1.38, J1.40, J5.3, J7.3, J9.3, J10.4, J11.4, J12.3, J13.2, J14.1, R1.1
/HOZ_1A: J1.11, J3.2
/HOZ_1B: J1.9, J3.1
/HOZ_2A: J1.13, J3.3
/HOZ_2B: J1.15, J3.4
/LED_DATA_IN: J1.12, J10.2
/LED_DATA_OUT: J1.14, J11.3
/LED_LOOP: J10.3, J11.2
/ROLL_1A: J1.3, J2.2
/ROLL_1B: J1.1, J2.1
/ROLL_2A: J1.5, J2.3
/ROLL_2B: J1.7, J2.4
/SERVO_FLAG: J1.10, J5.2
/SERVO_PITCH: J1.6, J9.2
/SERVO_RATE: J1.8, J7.2
/TEST_PUSH: J1.22, J13.1
/VER_1A: J1.19, J4.2
/VER_1B: J1.17, J4.1
/VER_2A: J1.21, J4.3
/VER_2B: J1.23, J4.4
/WL_1A: J1.27, J6.2
/WL_1B: J1.25, J6.1
/WL_2A: J1.29, J6.3
/WL_2B: J1.31, J6.4
/ZERO_IR: J1.4, J12.2
unnamed: D1.1 (K), R1.2

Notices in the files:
PCBs/Power_Distro_PCB_V2/Power Distro PCB V2.kicad_pcb:
© L. Walker 2021
